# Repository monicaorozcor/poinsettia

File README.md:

# Poinsettia PCB
This PCB Design is a little project about Christmas. You can use it to decorate your chistmas tree.
# Description
This PCB is a ornament to decorate your Christmas tree. It will turn on leds.
# Components list
Electronic components list used:
* 5 RGB0807
* 1 Batt HLD-001 
* 1 Switch 1825232-1

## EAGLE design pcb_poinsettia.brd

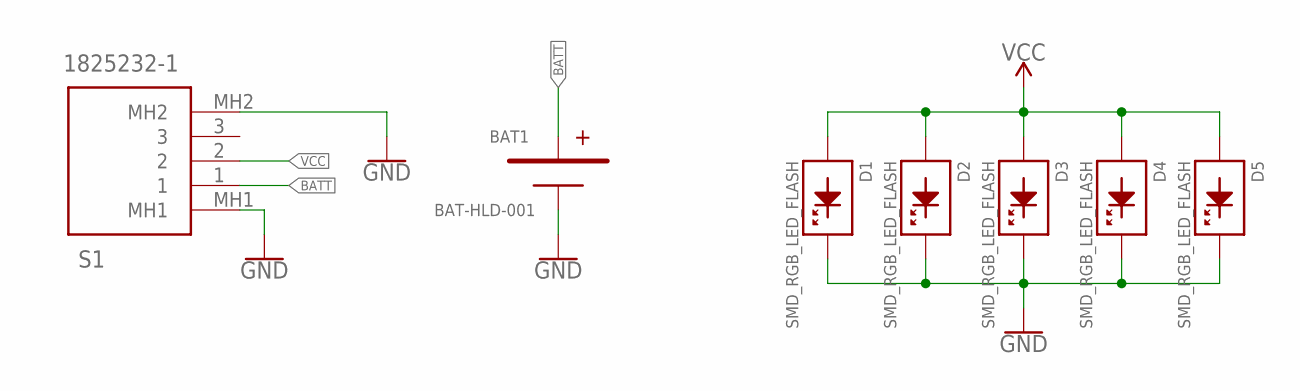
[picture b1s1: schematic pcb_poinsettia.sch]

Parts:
BAT1: BAT-HLD-001; BATHLD001
D1, D2, D3, D4, D5: SMD_RGB_LED_FLASH; SMD_RGB_LED_0807
S1: 1825232-1; 18252321

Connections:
BATT: BAT1.1, BAT1.2, S1.1
GND: BAT1.3 (N), D1.3 (K), D1.4 (K), D2.3 (K), D2.4 (K), D3.3 (K), D3.4 (K), D4.3 (K), D4.4 (K), D5.3 (K), D5.4 (K), S1.MH1, S1.MH2
VCC: D1.1 (A), D1.2 (A), D2.1 (A), D2.2 (A), D3.1 (A), D3.2 (A), D4.1 (A), D4.2 (A), D5.1 (A), D5.2 (A), S1.2

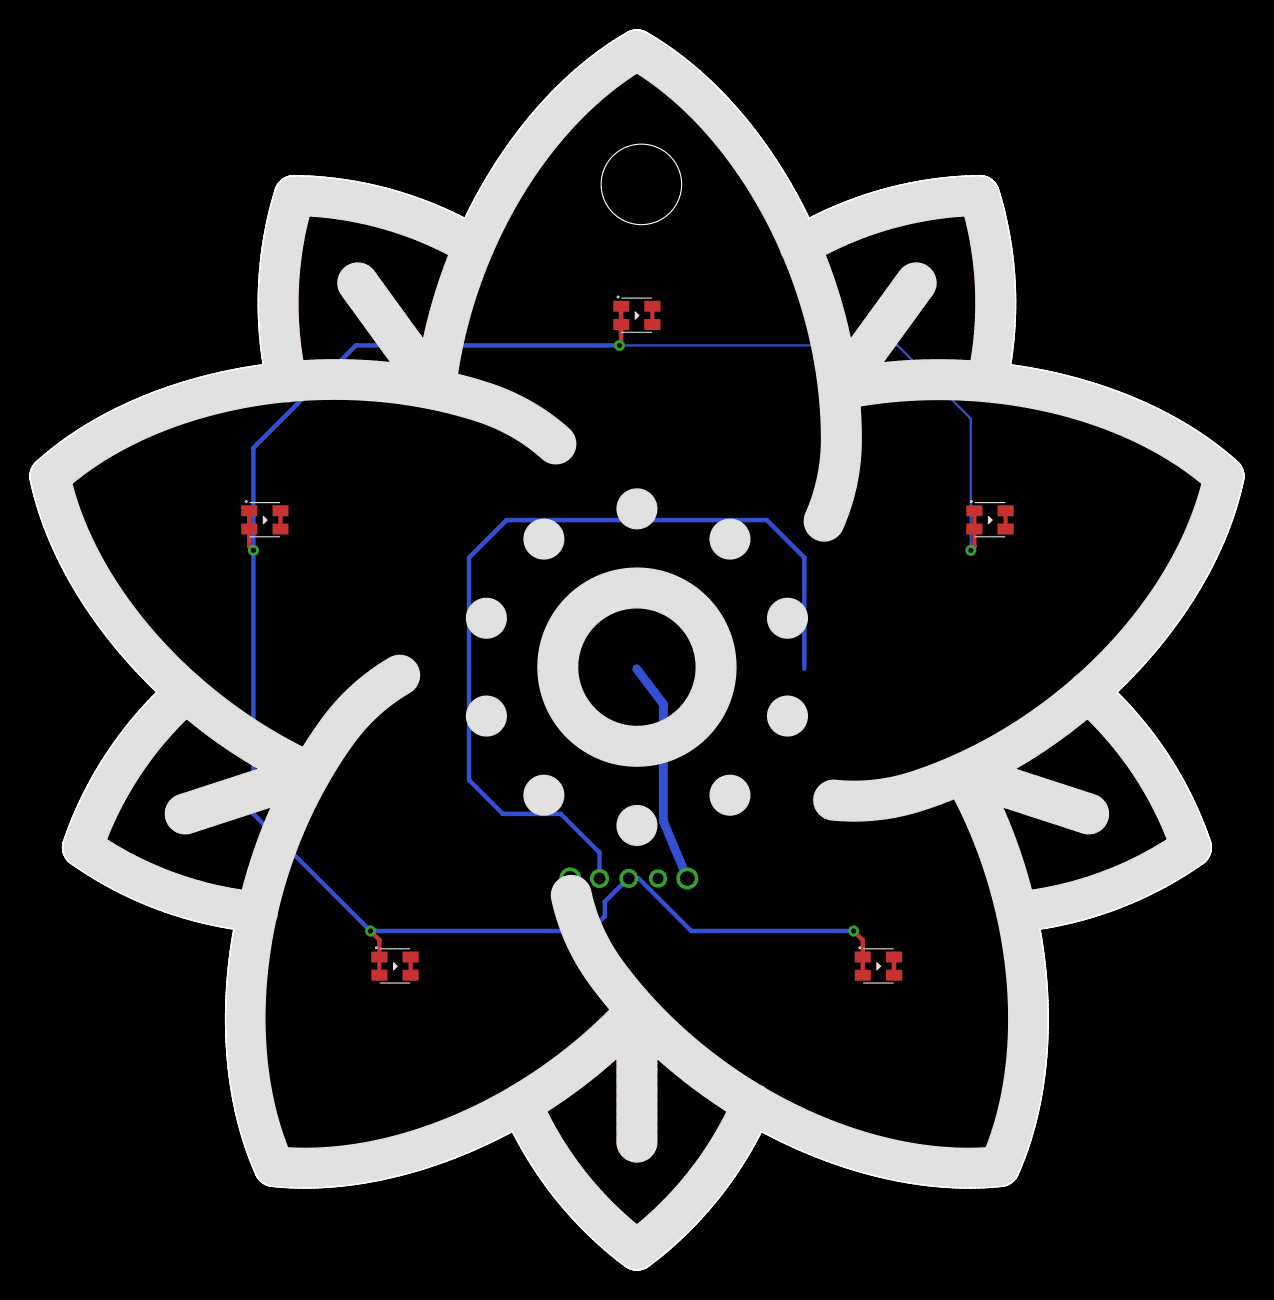
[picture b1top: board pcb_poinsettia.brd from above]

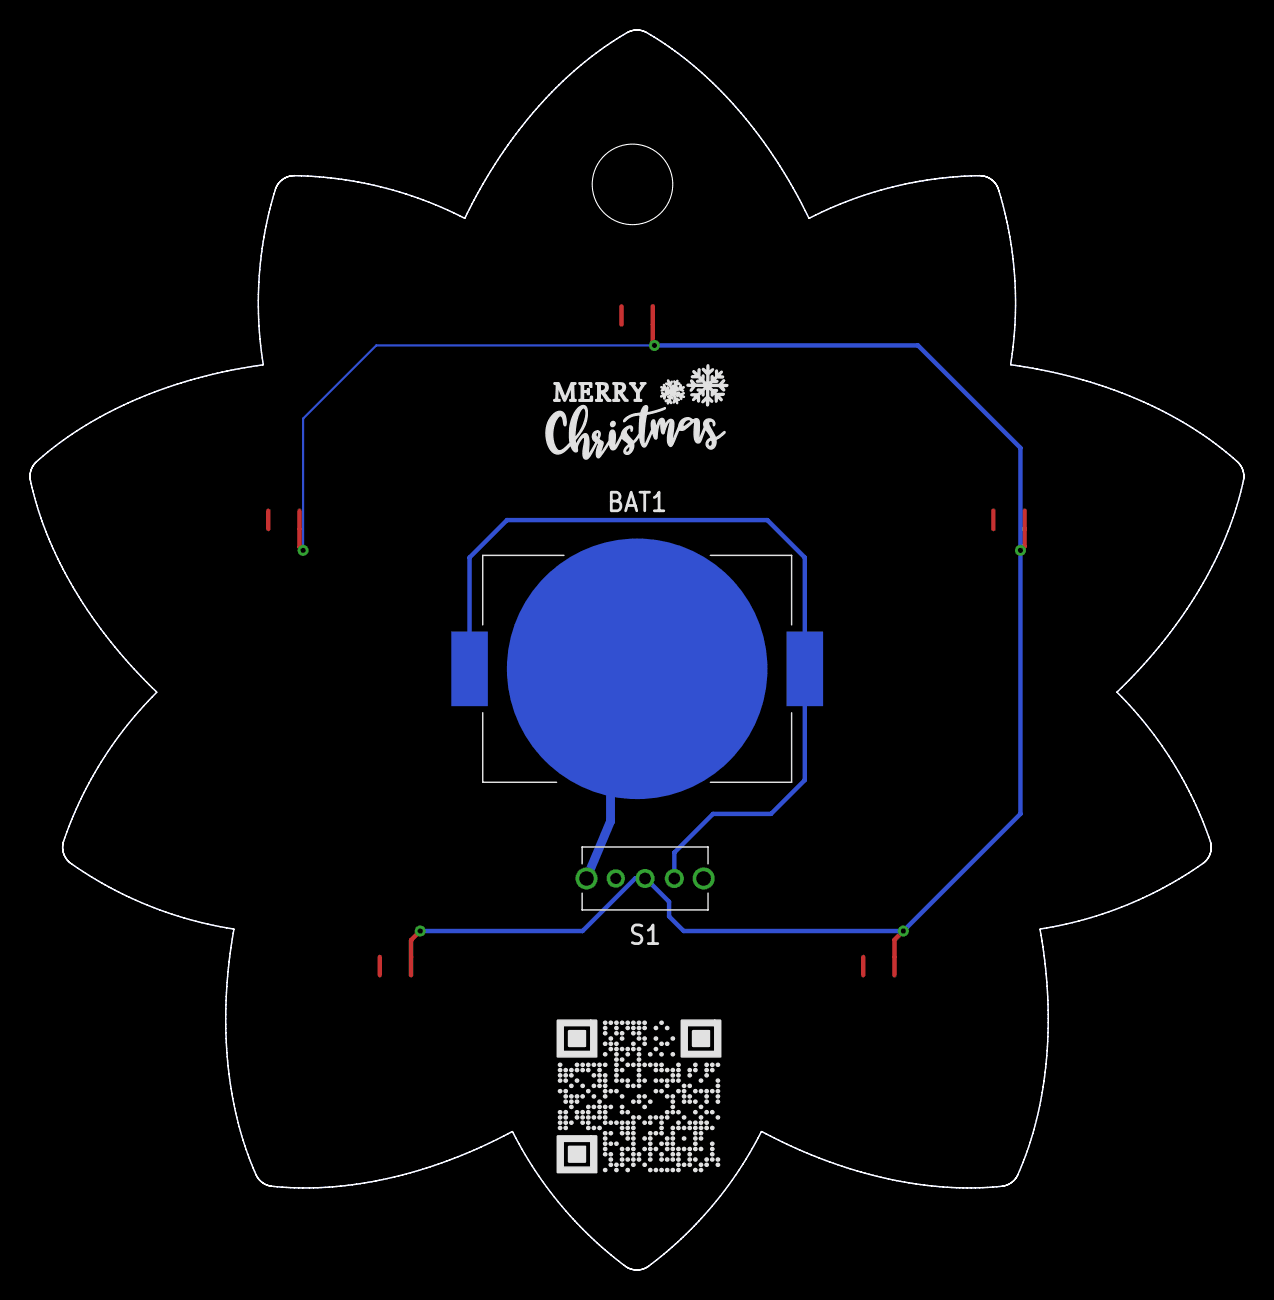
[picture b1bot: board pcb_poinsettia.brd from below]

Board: 2 copper layers, 82.9 x 84.7 mm, 7 parts (2 on the bottom side), 3 nets.
